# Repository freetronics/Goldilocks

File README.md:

Freetronics Goldilocks
======================
Copyright 2013 Freetronics Pty Ltd  
Freetronics site:  www.freetronics.com  
Freetronics email: info@freetronics.com  

Add Description

Features:

 * Prototyping area
 * LEDs visible on the edge
 * Mini-USB Connector
 * Overlay guide where you need it (both top and bottom)
 * D13 pin works for everything
 * Mounting holes and power pads
 * All connections in the same place

You can view more online at:

  http://www.freetronics.com/goldilocks

The "docs" folder within this repository includes a handy copy of the
schematic in PDF format, images of the pcb, and our Getting Started
guide that ships with each board.

INSTALLATION
------------
The design is saved as an EAGLE project. EAGLE PCB design software is
available from www.cadsoftusa.com free for non-commercial use. To use
this project download it and place the directory containing these files
into the "eagle" directory on your computer. Then open EAGLE and
navigate to Projects -> eagle -> Goldilocks.

DISTRIBUTION
------------
The specific terms of distribution of this project are governed by the
license referenced below.

LICENSE
-------
Licensed under the TAPR Open Hardware License (www.tapr.org/OHL).
The "license" folder within this repository also contains a copy of
this license in plain text format.

CREDITS
-------
The Eleven was designed Jonathan Oxer (jon@freetronics.com) in
collaboration with Phillip Stevens.

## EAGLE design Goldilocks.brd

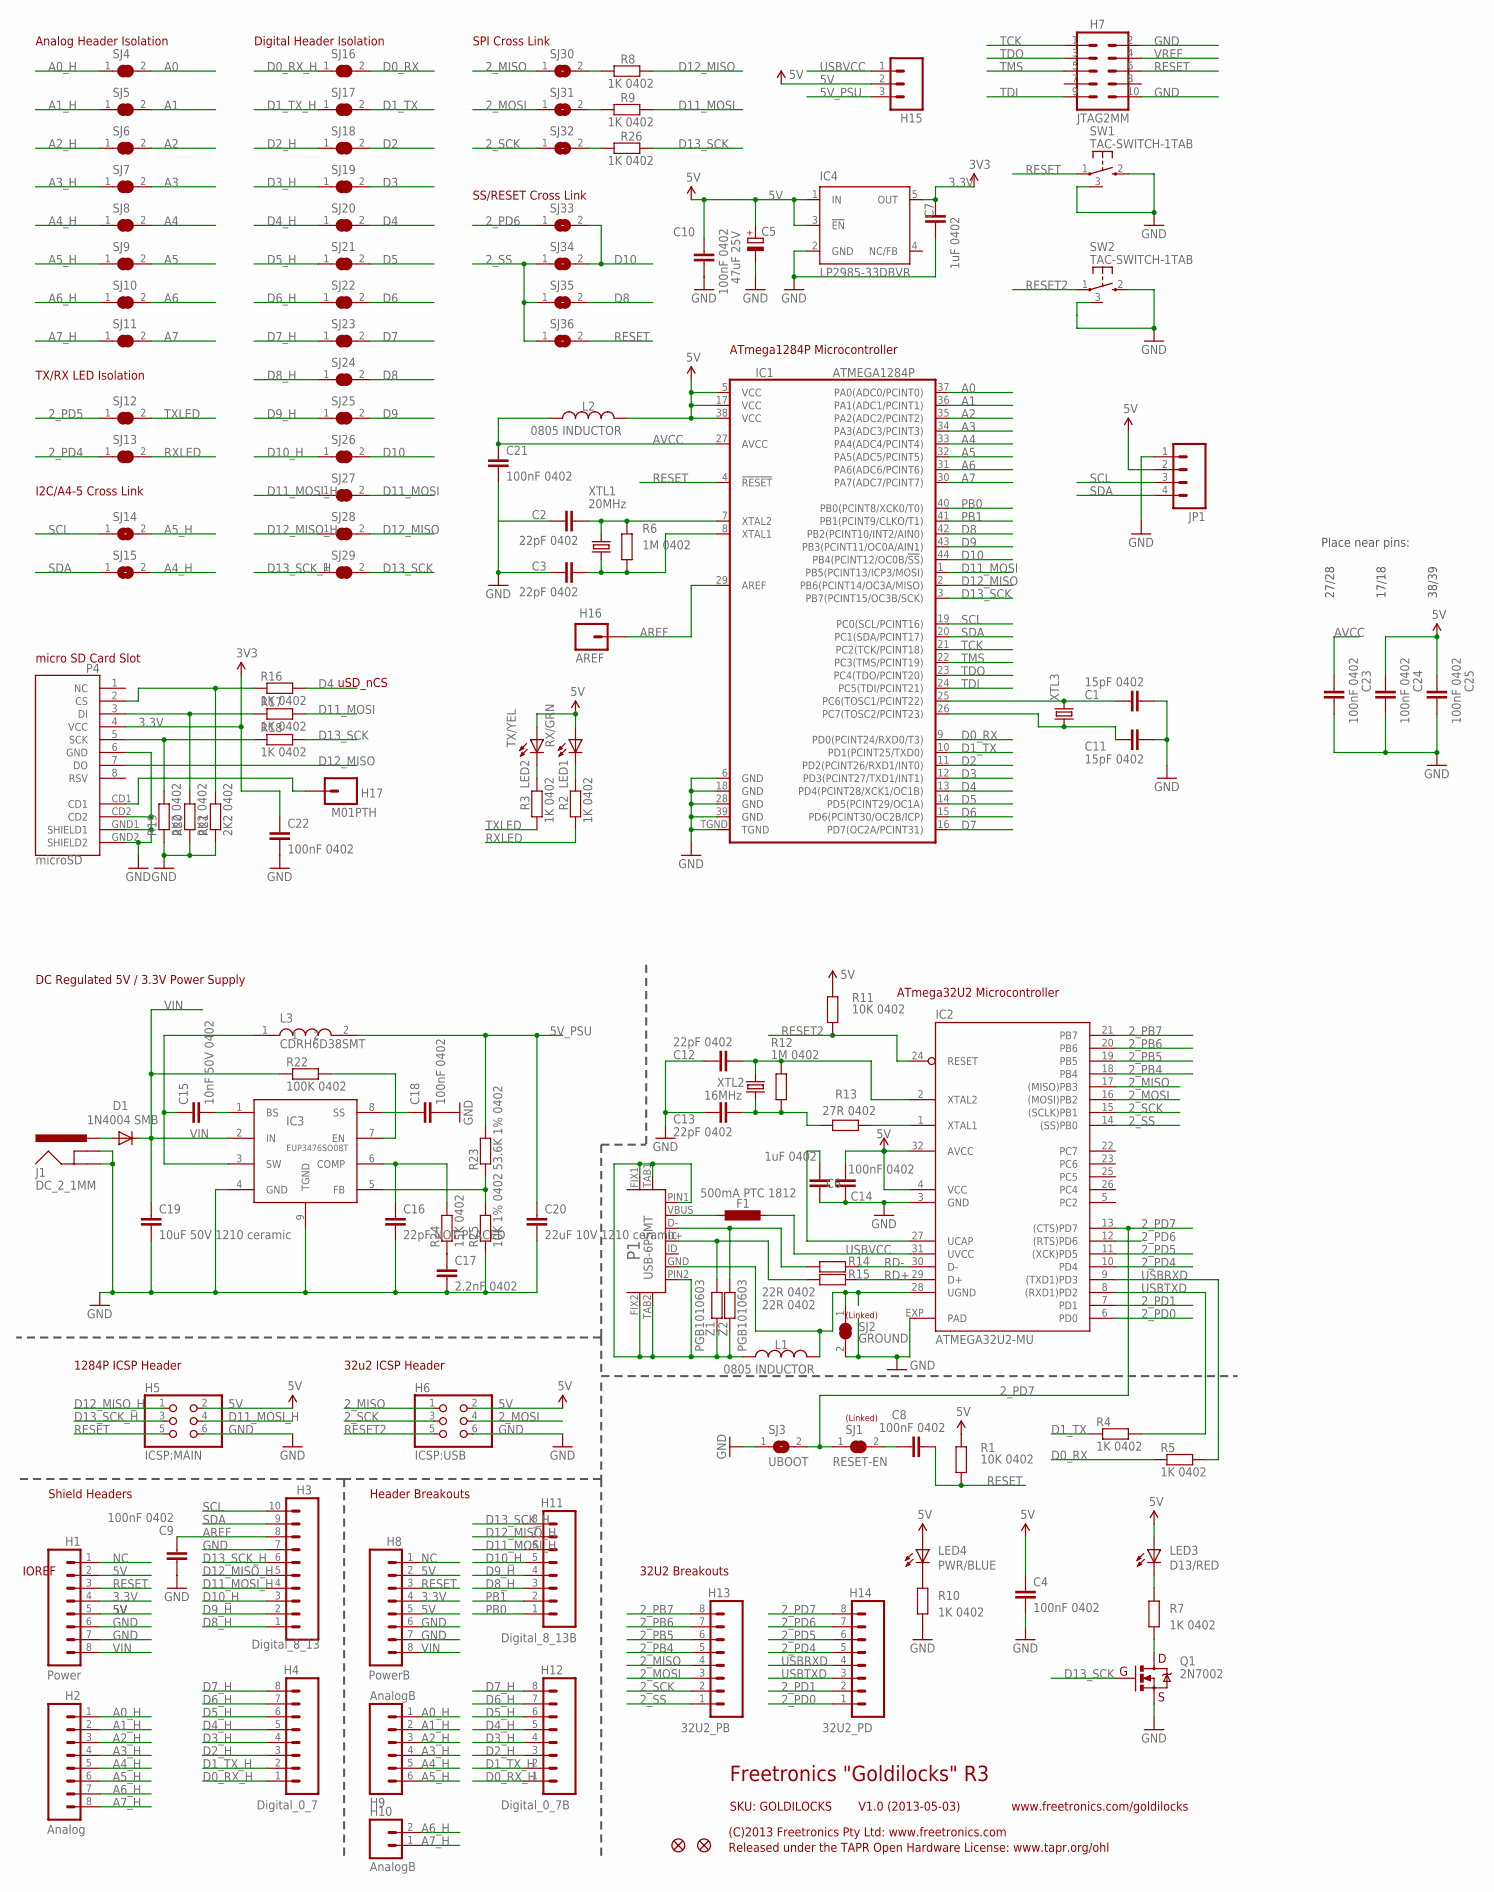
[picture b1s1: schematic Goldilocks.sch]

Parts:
C1, C11: 15pF 0402; 0402C
C2, C3, C12, C13: 22pF 0402; 0402C
C4, C8, C9, C10, C14, C18, C21, C22, C23, C24, C25: 100nF 0402; 0402C
C5: 47uF 25V; PANASONIC_D
C6, C7: 1uF 0402; 0402C
C15: 10nF 50V 0402; 0402C
C16: 22pF NOT PLACED; 0402C
C17: 2.2nF 0402; 0402C
C19: 10uF 50V 1210 ceramic; C1210
C20: 22uF 10V 1210 ceramic; C1210
D1: 1N4004 SMB; SMB-DIODE
F1: 500mA PTC 1812; L1812
H1: Power; 1X08
H2: Analog; 1X08
H3: Digital_8_13; 1X10
H4: Digital_0_7; 1X08
H5: ICSP:MAIN; 2X03
H6: ICSP:USB; 2X03
H7: JTAG2MM; SAMTEC-TMM-DOUBLE
H8: PowerB; 1X08
H9: AnalogB; 1X06
H10: AnalogB; 1X02
H11: Digital_8_13B; 1X08
H12: Digital_0_7B; 1X08
H13: 32U2_PB; 1X08
H14: 32U2_PD; 1X08
H15: M03PTH; 1X03
H16: AREF; 1X01
H17: M01PTH; 1X01
IC1: ATMEGA1284P; QFN-44M1
IC2: ATMEGA32U2-MU; ATMEL_QFN32
IC3: EUP3476SO08T; SO08T
IC4: LP2985-33DBVR; TEXAS_SOT23-DBV
J1: DC_2_1MM; POWER_JACK_PTH
JP1: M04PTH; 1X04
L1, L2: 0805 INDUCTOR; 0805-LARGE
L3: CDRH6D38SMT; CDRH
LED1: RX/GRN; LED-0402
LED2: TX/YEL; LED-0402
LED3: D13/RED; LED-0402
LED4: PWR/BLUE; LED-0402
P1: USB-6PSMT; USB-MICROB-MB05PMXX
P4: microSD; MICRO-SD-SOCKET-PP
Q1: 2N7002; SOT23-3
R1, R11: 10K 0402; 0402
R2, R3, R4, R5, R7, R8, R9, R10, R16, R17, R18, R26: 1K 0402; 0402
R6, R12: 1M 0402; 0402
R13: 27R 0402; 0402
R14, R15: 22R 0402; 0402
R19, R20, R21: 2K2 0402; 0402
R22: 100K 0402; 0402
R23: 53.6K 1% 0402; 0402
R24: 15K 0402; 0402
R25: 10K 1% 0402; 0402
SJ1: RESET-EN; SJC
SJ2: GROUND; SJC
SJ3: UBOOT; SJ
SJ4, SJ5, SJ6, SJ7, SJ8, SJ9, SJ10, SJ11, SJ12, SJ13, SJ16, SJ17, SJ18, SJ19, SJ20, SJ21, SJ22, SJ23, SJ24, SJ25, SJ26, SJ27, SJ28, SJ29: SJC0402; 0402SJC
SJ14, SJ15: SJ
SJ30: MISO; SJ
SJ31: MOSI; SJ
SJ32: SCK; SJ
SJ33, SJ34, SJ35, SJ36: SJN; SJ
SW1, SW2: TAC-SWITCH-1TAB; TACT-VERT-1TAB
U$5, U$14: FIDUCIAL1X2.5; FIDUCIAL-1X2.5
XTL1: 20MHz; HC49U-V
XTL2: 16MHz; HC49U-V
XTL3: CRYSTALTC38H; TC38H
Z1, Z2: PGB1010603; 0603

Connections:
2_MISO: H6.1, H13.4, IC2.17 ((MISO)PB3), SJ30.1
2_MOSI: H6.4, H13.3, IC2.16 ((MOSI)PB2), SJ31.1
2_PB4: H13.5, IC2.18 (PB4)
2_PB5: H13.6, IC2.19 (PB5)
2_PB6: H13.7, IC2.20 (PB6)
2_PB7: H13.8, IC2.21 (PB7)
2_PD0: H14.1, IC2.6 (PD0)
2_PD1: H14.2, IC2.7 (PD1)
2_PD4: H14.5, IC2.10 (PD4), SJ13.1
2_PD5: H14.6, IC2.11 ((XCK)PD5), SJ12.1
2_PD6: H14.7, IC2.12 ((RTS)PD6), SJ33.1
2_PD7: H14.8, IC2.13 ((CTS)PD7), SJ1.1, SJ3.2
2_SCK: H6.3, H13.2, IC2.15 ((SCLK)PB1), SJ32.1
2_SS: H13.1, IC2.14 ((SS)PB0), SJ34.1, SJ35.1, SJ36.1
3.3V: C7.2, C22.1, H1.4, H8.4, IC4.5 (OUT), P4.4 (VCC)
5V: C4.1, C5.+, C10.1, C14.1, C24.1, C25.1, H1.2, H1.5, H5.2, H6.2, H8.2, H8.5, H15.2, IC1.5 (VCC), IC1.17 (VCC), IC1.38 (VCC), IC2.4 (VCC), IC2.32 (AVCC), IC4.1 (IN), IC4.3 (!EN), JP1.2, L2.2, LED1.A, LED2.A, LED3.A, LED4.A, R1.2, R11.2
5V_PSU: C20.1, H15.3, L3.2, R23.2
A0: IC1.37 (PA0(ADC0/PCINT0)), SJ4.2
A0_H: H2.1, H9.1, SJ4.1
A1: IC1.36 (PA1(ADC1/PCINT1)), SJ5.2
A1_H: H2.2, H9.2, SJ5.1
A2: IC1.35 (PA2(ADC2/PCINT2)), SJ6.2
A2_H: H2.3, H9.3, SJ6.1
A3: IC1.34 (PA3(ADC3/PCINT3)), SJ7.2
A3_H: H2.4, H9.4, SJ7.1
A4: IC1.33 (PA4(ADC4/PCINT4)), SJ8.2
A4_H: H2.5, H9.5, SJ8.1, SJ15.2
A5: IC1.32 (PA5(ADC5/PCINT5)), SJ9.2
A5_H: H2.6, H9.6, SJ9.1, SJ14.2
A6: IC1.31 (PA6(ADC6/PCINT6)), SJ10.2
A6_H: H2.7, H10.2, SJ10.1
A7: IC1.30 (PA7(ADC7/PCINT7)), SJ11.2
A7_H: H2.8, H10.1, SJ11.1
AREF: C9.1, H3.8, H16.1, IC1.29 (AREF)
AVCC: C21.1, C23.1, IC1.27 (AVCC), L2.1
D0_RX: IC1.9 (PD0(PCINT24/RXD0/T3)), R5.1, SJ16.2
D0_RX_H: H4.1, H12.1, SJ16.1
D1_TX: IC1.10 (PD1(PCINT25/TXD0)), R4.1, SJ17.2
D1_TX_H: H4.2, H12.2, SJ17.1
D2: IC1.11 (PD2(PCINT26/RXD1/INT0)), SJ18.2
D2_H: H4.3, H12.3, SJ18.1
D3: IC1.12 (PD3(PCINT27/TXD1/INT1)), SJ19.2
D3_H: H4.4, H12.4, SJ19.1
D4: IC1.13 (PD4(PCINT28/XCK1/OC1B)), R16.2, SJ20.2
D4_H: H4.5, H12.5, SJ20.1
D5: IC1.14 (PD5(PCINT29/OC1A)), SJ21.2
D5_H: H4.6, H12.6, SJ21.1
D6: IC1.15 (PD6(PCINT30/OC2B/ICP)), SJ22.2
D6_H: H4.7, H12.7, SJ22.1
D7: IC1.16 (PD7(OC2A/PCINT31)), SJ23.2
D7_H: H4.8, H12.8, SJ23.1
D8: IC1.42 (PB2(PCINT10/INT2/AIN0)), SJ24.2, SJ35.2
D8_H: H3.1, H11.3, SJ24.1
D9: IC1.43 (PB3(PCINT11/OC0A/AIN1)), SJ25.2
D9_H: H3.2, H11.4, SJ25.1
D10: IC1.44 (PB4(PCINT12/OC0B/!SS!)), SJ26.2, SJ33.2, SJ34.2
D10_H: H3.3, H11.5, SJ26.1
D11_MOSI: H5.4, IC1.1 (PB5(PCINT13/ICP3/MOSI)), R9.2, R17.2, SJ27.2
D11_MOSI_H: H3.4, H11.6, SJ27.1
D12_MISO: H5.1, IC1.2 (PB6(PCINT14/OC3A/MISO)), P4.7 (DO), R8.2, SJ28.2
D12_MISO_H: H3.5, H11.7, SJ28.1
D13_SCK: H5.3, IC1.3 (PB7(PCINT15/OC3B/SCK)), Q1.1 (G), R18.2, R26.2, SJ29.2
D13_SCK_H: H3.6, H11.8, SJ29.1
GND: C1.2, C2.1, C3.1, C4.2, C5.-, C6.2, C7.1, C9.2, C10.2, C11.2, C12.1, C13.1, C14.2, C16.2, C17.2, C18.2, C19.2, C20.2, C21.2, C22.2, C23.2, C24.2, C25.2, H1.6, H1.7, H3.7, H5.6, H6.6, H7.2, H7.10, H8.6, H8.7, IC1.6 (GND), IC1.18 (GND), IC1.28 (GND), IC1.39 (GND), IC1.TGND, IC2.3 (GND), IC2.EXP (PAD), IC3.4 (GND), IC3.9 (TGND), IC4.2 (GND), J1.GND, J1.GNDBREAK, JP1.1, P4.6 (GND), P4.CD2, P4.GND1 (SHIELD1), P4.GND2 (SHIELD2), Q1.2 (S), R10.1, R19.1, R20.1, R21.1, R25.1, SJ2.2, SJ3.1, SW1.2, SW1.3, SW2.2, SW2.3
unnamed: C8.1, SJ1.2
unnamed: IC2.1 (XTAL1), R13.1
unnamed: L1.1, P1.FIX1, P1.FIX2, P1.PIN1, P1.PIN2, P1.TAB1, P1.TAB2, Z1.2, Z2.2
unnamed: LED3.C, R7.2
unnamed: C2.2, IC1.7 (XTAL2), R6.2, XTL1.2
unnamed: Q1.3 (D), R7.1
unnamed: C3.2, IC1.8 (XTAL1), R6.1, XTL1.1
unnamed: D1.A, J1.PWR
unnamed: R8.1, SJ30.2
unnamed: LED1.C, R2.2
unnamed: LED2.C, R3.2
unnamed: LED4.C, R10.2
unnamed: P1.D+, R15.2, Z1.1
unnamed: P1.D-, R14.2, Z2.1
unnamed: C1.1, IC1.25 (PC6(TOSC1/PCINT22)), XTL3.2
unnamed: C11.1, IC1.26 (PC7(TOSC2/PCINT23)), XTL3.1
unnamed: C15.2, IC3.1 (BS)
unnamed: R9.1, SJ31.2
unnamed: C15.1, IC3.3 (SW), L3.1
unnamed: C17.1, R24.1
unnamed: IC3.5 (FB), R23.1, R25.2
unnamed: C18.1, IC3.8 (SS)
unnamed: R26.1, SJ32.2
unnamed: IC3.7 (EN), R22.2
unnamed: C16.1, IC3.6 (COMP), R24.2
unnamed: C12.2, IC2.2 (XTAL2), R12.2, XTL2.2
unnamed: C13.2, R12.1, R13.2, XTL2.1
unnamed: F1.1, P1.VBUS
unnamed: C6.1, IC2.27 (UCAP)
unnamed: P4.2 (CS), R16.1, R21.2
unnamed: P4.3 (DI), R17.1, R20.2
unnamed: P4.5 (SCK), R18.1, R19.2
unnamed: H17.1, P4.CD1
NC: H1.1, H8.1
PB0: H11.1, IC1.40 (PB0(PCINT8/XCK0/T0))
PB1: H11.2, IC1.41 (PB1(PCINT9/CLKO/T1))
RD+: IC2.29 (D+), R15.1
RD-: IC2.30 (D-), R14.1
RESET: C8.2, H1.3, H5.5, H7.6, H8.3, IC1.4 (!RESET), R1.1, SJ36.2, SW1.1
RESET2: H6.5, IC2.24 (RESET), R11.1, SW2.1
RXLED: R2.1, SJ13.2
SCL: H3.10, IC1.19 (PC0(SCL/PCINT16)), JP1.3, SJ14.1
SDA: H3.9, IC1.20 (PC1(SDA/PCINT17)), JP1.4, SJ15.1
TCK: H7.1, IC1.21 (PC2(TCK/PCINT18))
TDI: H7.9, IC1.24 (PC5(TDI/PCINT21))
TDO: H7.3, IC1.23 (PC4(TDO/PCINT20))
TMS: H7.5, IC1.22 (PC3(TMS/PCINT19))
TXLED: R3.1, SJ12.2
UGND: IC2.28 (UGND), L1.2, P1.GND, SJ2.1
USBRXD: H14.4, IC2.9 ((TXD1)PD3), R5.2
USBTXD: H14.3, IC2.8 ((RXD1)PD2), R4.2
USBVCC: F1.2, H15.1, IC2.31 (UVCC)
VIN: C19.1, D1.C, H1.8, H8.8, IC3.2 (IN), R22.1
VREF: H7.4

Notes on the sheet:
DC Regulated 5V / 3.3V Power Supply
ATmega1284P Microcontroller
ATmega32U2 Microcontroller
Freetronics "Goldilocks" R3
V1.0 (2013-05-03)
SKU: GOLDILOCKS
(C)2013 Freetronics Pty Ltd: www.freetronics.com
Released under the TAPR Open Hardware License: www.tapr.org/ohl
www.freetronics.com/goldilocks
(Linked)
IOREF
uSD_nCS
micro SD Card Slot
TX/RX LED Isolation
I2C/A4-5 Cross Link
Digital Header Isolation
Analog Header Isolation
SPI Cross Link
SS/RESET Cross Link
Shield Headers
Header Breakouts
1284P ICSP Header
32u2 ICSP Header
32U2 Breakouts
27/28
17/18
38/39
Place near pins:

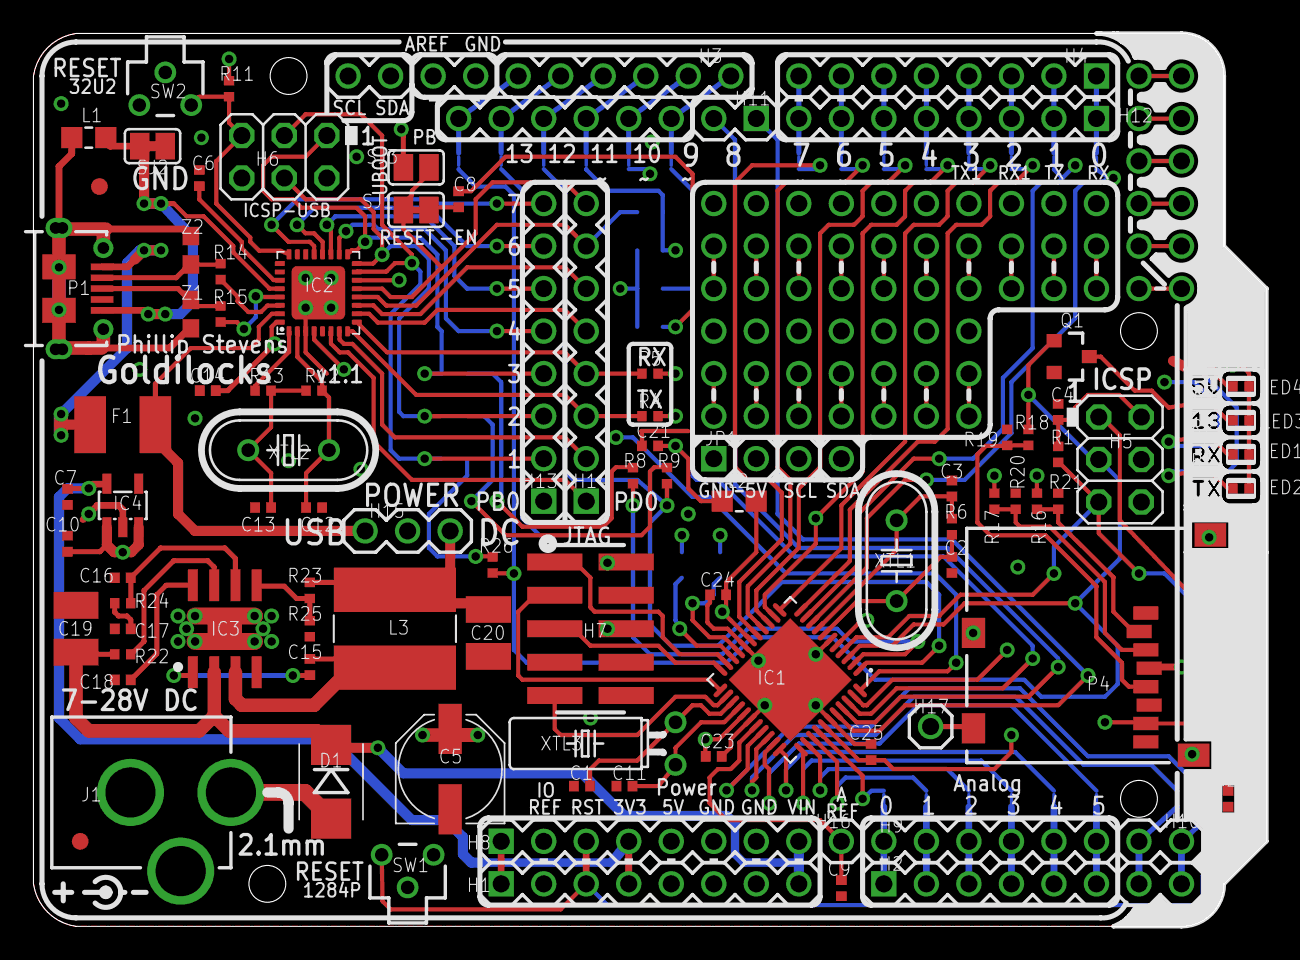
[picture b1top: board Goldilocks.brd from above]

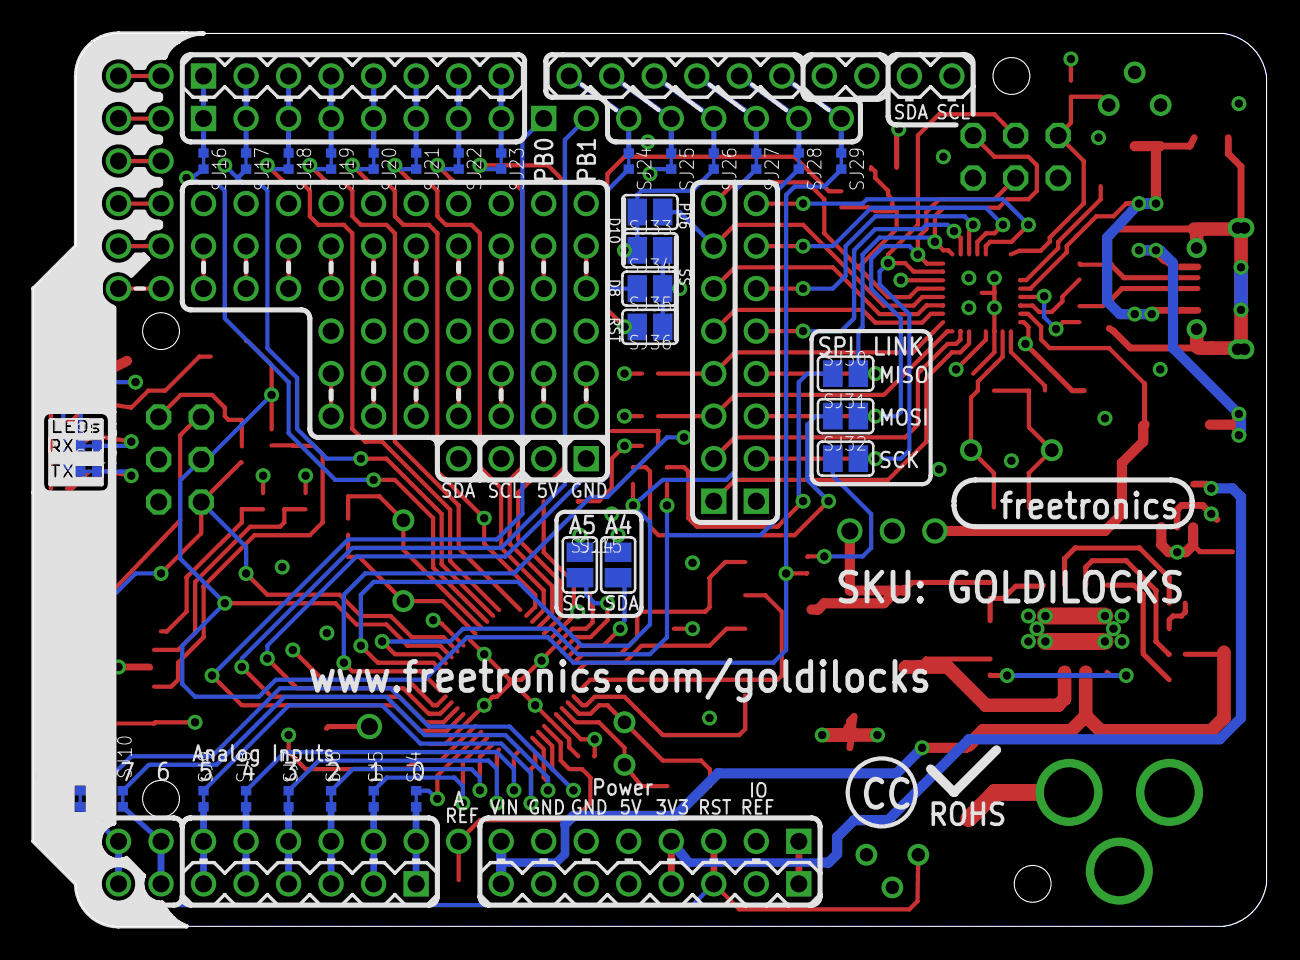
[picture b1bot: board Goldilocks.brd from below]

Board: 4 copper layers, 73.7 x 53.3 mm, 131 parts (33 on the bottom side), 117 nets.

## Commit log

2013-03-22 Initial project setup
2013-05-01 Routing
2013-05-02 Switched to 4 layer PCB
2013-05-03 Hopefully ready for v1.0 release
2013-10-13 v1.1 release for production

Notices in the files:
parts and their libraries:
freetronics-original: Licensing: CC v3.0 Share-Alike You are welcome to use this library for commercial purposes.
